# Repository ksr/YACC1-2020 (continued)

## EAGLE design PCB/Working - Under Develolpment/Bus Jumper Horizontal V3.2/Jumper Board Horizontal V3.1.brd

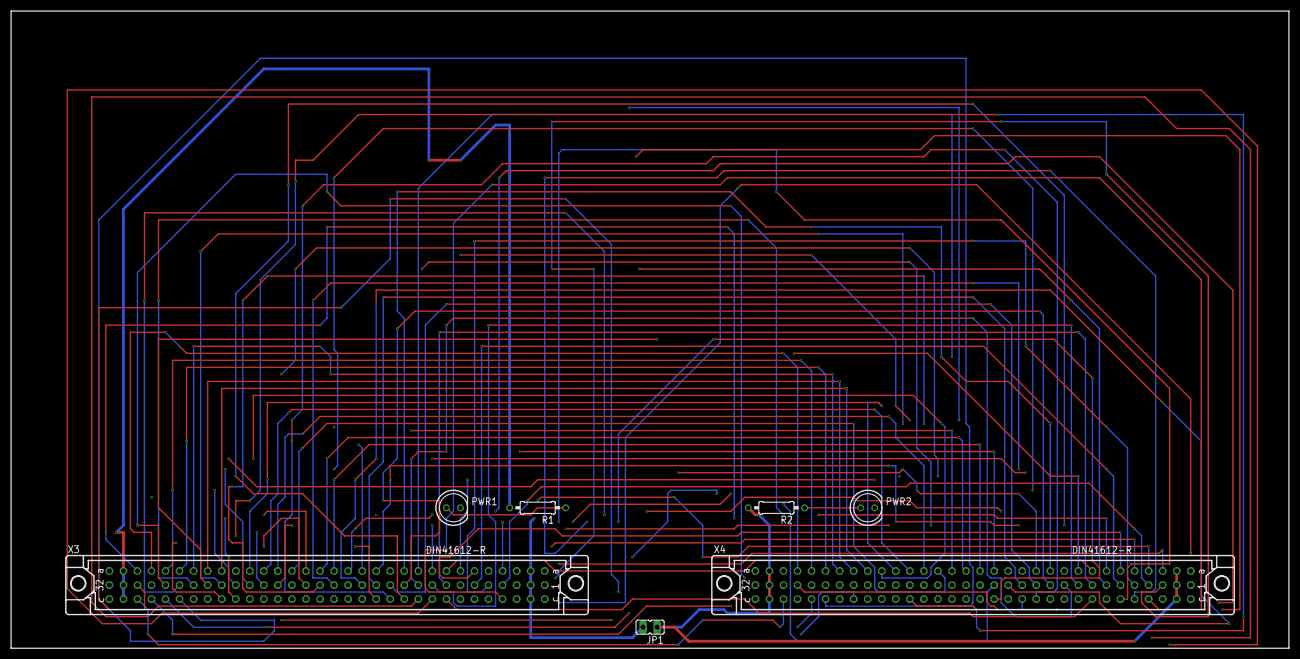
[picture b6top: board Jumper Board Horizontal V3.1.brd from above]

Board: 4 copper layers, 231.1 x 115.2 mm, 7 parts (0 on the bottom side), 89 nets.

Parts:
JP1: JP1
PWR1, PWR2: LED5MM
R1, R2: 330; 0207/10
X3, X4: MABC96R

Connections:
GND: PWR1.K, PWR2.K, X3.A1, X3.A32, X3.B1, X3.B32, X3.C1, X3.C32, X4.A1, X4.A32, X4.B1, X4.B32, X4.C1, X4.C32
unnamed: X3.A3, X4.A3
unnamed: X3.A4, X4.A4
unnamed: X3.A5, X4.A5
unnamed: X3.A6, X4.A6
unnamed: X3.A7, X4.A7
unnamed: X3.A8, X4.A8
unnamed: X3.A9, X4.A9
unnamed: X3.A10, X4.A10
unnamed: X3.A11, X4.A11
unnamed: X3.A12, X4.A12
unnamed: X3.A13, X4.A13
unnamed: X3.A14, X4.A14
unnamed: X3.A15, X4.A15
unnamed: X3.A16, X4.A16
unnamed: X3.A17, X4.A17
unnamed: X3.A18, X4.A18
unnamed: X3.A19, X4.A19
unnamed: X3.A20, X4.A20
unnamed: X3.A21, X4.A21
unnamed: X3.A22, X4.A22
unnamed: X3.A23, X4.A23
unnamed: X3.A24, X4.A24
unnamed: X3.A25, X4.A25
unnamed: X3.A26, X4.A26
unnamed: X3.A27, X4.A27
unnamed: X3.A28, X4.A28
unnamed: X3.A29, X4.A29
unnamed: X3.A30, X4.A30
unnamed: PWR1.A, R1.1
unnamed: PWR2.A, R2.1
unnamed: X3.B3, X4.B3
unnamed: X3.B4, X4.B4
unnamed: X3.B5, X4.B5
unnamed: X3.B6, X4.B6
unnamed: X3.B7, X4.B7
unnamed: X3.B8, X4.B8
unnamed: X3.B9, X4.B9
unnamed: X3.B10, X4.B10
unnamed: X3.B11, X4.B11
unnamed: X3.B12, X4.B12
unnamed: X3.B13, X4.B13
unnamed: X3.B14, X4.B14
unnamed: X3.B15, X4.B15
unnamed: X3.B16, X4.B16
unnamed: X3.B17, X4.B17
unnamed: X3.B18, X4.B18
unnamed: X3.B19, X4.B19
unnamed: X3.B20, X4.B20
unnamed: X3.B21, X4.B21
unnamed: X3.B22, X4.B22
unnamed: X3.B23, X4.B23
unnamed: X3.B24, X4.B24
unnamed: X3.B25, X4.B25
unnamed: X3.B26, X4.B26
unnamed: X3.B27, X4.B27
unnamed: X3.B28, X4.B28
unnamed: X3.B29, X4.B29
unnamed: X3.B30, X4.B30
unnamed: X3.C3, X4.C3
unnamed: X3.C4, X4.C4
unnamed: X3.C5, X4.C5
unnamed: X3.C6, X4.C6
unnamed: X3.C7, X4.C7
unnamed: X3.C8, X4.C8
unnamed: X3.C9, X4.C9
unnamed: X3.C10, X4.C10
unnamed: X3.C11, X4.C11
unnamed: X3.C12, X4.C12
unnamed: X3.C13, X4.C13
unnamed: X3.C14, X4.C14
unnamed: X3.C15, X4.C15
unnamed: X3.C16, X4.C16
unnamed: X3.C17, X4.C17
unnamed: X3.C18, X4.C18
unnamed: X3.C19, X4.C19
unnamed: X3.C20, X4.C20
unnamed: X3.C21, X4.C21
unnamed: X3.C22, X4.C22
unnamed: X3.C23, X4.C23
unnamed: X3.C24, X4.C24
unnamed: X3.C25, X4.C25
unnamed: X3.C26, X4.C26
unnamed: X3.C27, X4.C27
unnamed: X3.C28, X4.C28
unnamed: X3.C29, X4.C29
unnamed: X3.C30, X4.C30
V1: JP1.2, R1.2, X3.A2, X3.A31, X3.B2, X3.B31, X3.C2, X3.C31
V2: JP1.1, R2.2, X4.A2, X4.A31, X4.B2, X4.B31, X4.C2, X4.C31
